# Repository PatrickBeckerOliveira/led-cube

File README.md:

# LED Cube 4×4×4 — ESP32-C3 + BLE

A 64-LED cube controlled by an ESP32-C3 SuperMini, two daisy-chained TPIC6B595 shift registers, and four layers switched by NPN-driven P-channel MOSFETs. Arduino firmware with BLE commands and five sequential animation effects.

## Firmware

Open `led_cube_ble/led_cube_ble.ino` in the Arduino IDE with the **esp32 board package by Espressif Systems** installed. Select the appropriate ESP32-C3 board (ESP32C3 Dev Module where applicable) and serial port. The code uses the BLE library included in the ESP32 package, along with `<atomic>`.

This version preserves the behavior of the animation code provided in the conversation. It has not been compiled or validated on hardware as part of this delivery; no specific ESP32 board package version has been pinned.

## Pin Mapping

| Function | GPIO |
|---|---:|
| TPIC SER IN / Data | 4 |
| TPIC SRCK / Clock | 5 |
| TPIC RCK / Latch | 6 |
| Layer 1 / NPN base | 7 |
| Layer 2 / NPN base | 8 |
| Layer 3 / NPN base | 9 |
| Layer 4 / NPN base | 10 |

Driving a layer GPIO high turns on the NPN transistor, which in turn switches on the P-channel MOSFET. A bit set to 1 in the TPIC activates the corresponding current-sinking output. The physical column order depends on the wiring.

## Using nRF Connect

1. Power on the board and connect to `Cubo_LED_4x4x4`.
2. Open service `6e400001-b5a3-f393-e0a9-e50e24dcca9e`.
3. Write UTF-8 text to characteristic `6e400002-b5a3-f393-e0a9-e50e24dcca9e`.

| Command | Action |
|---|---|
| `ON` or `1` | Start/restart the sequence |
| `OFF` or `0` | Turn off the cube |

The cube starts with all LEDs off when powered on. Disconnecting the app does not stop an ongoing animation; the device resumes advertising to allow reconnection. Commands do not require BLE authentication.

## Effects

1. Layers moving up and down.
2. Vertical columns lighting up in sequence.
3. Eight twinkling points.
4. Filling and emptying the cube layer by layer.
5. Three flashes followed by a pause.

The sequence repeats until `OFF` is received. Animation updates use `millis()`, and multiplexing uses `micros()`, with a nominal period of 2 ms per layer and a blanking interval of 30 µs. At most one layer is activated at a time. Timing and duration can be adjusted through the constants and the `updateAnimation()` function.

## Hardware Notes

- Cube supply: 5 V, with a common ground shared with the ESP. The power supply's current rating does not determine the current capacity of the SuperMini's PCB traces.
- GPIO8 and GPIO9 are boot strapping pins. The NPN base connections may interfere with startup, especially on GPIO9; using 10 kΩ resistors connected to the base showed no problems, lowering this value may cause issues.
- According to its datasheet, a TPIC6B595 powered at 5 V requires a minimum logic-high input of 0.85 × VCC = 4.25 V. Direct drive from 3.3 V GPIOs works but is not guaranteed; logic-level conversion should be implemented in the future.
- With 100 Ω column resistors and an LED forward voltage of approximately 3 V, the simplified estimate is 20 mA per LED and 320 mA for a full layer, plus the control electronics. Measure the actual current before sizing the power supply.

References: [TPIC6B595 — TI](https://www.ti.com/lit/ds/symlink/tpic6b595.pdf), [ESP32-C3 Boot Mode Selection — Espressif](https://docs.espressif.com/projects/esptool/en/latest/esp32c3/advanced-topics/boot-mode-selection.html).

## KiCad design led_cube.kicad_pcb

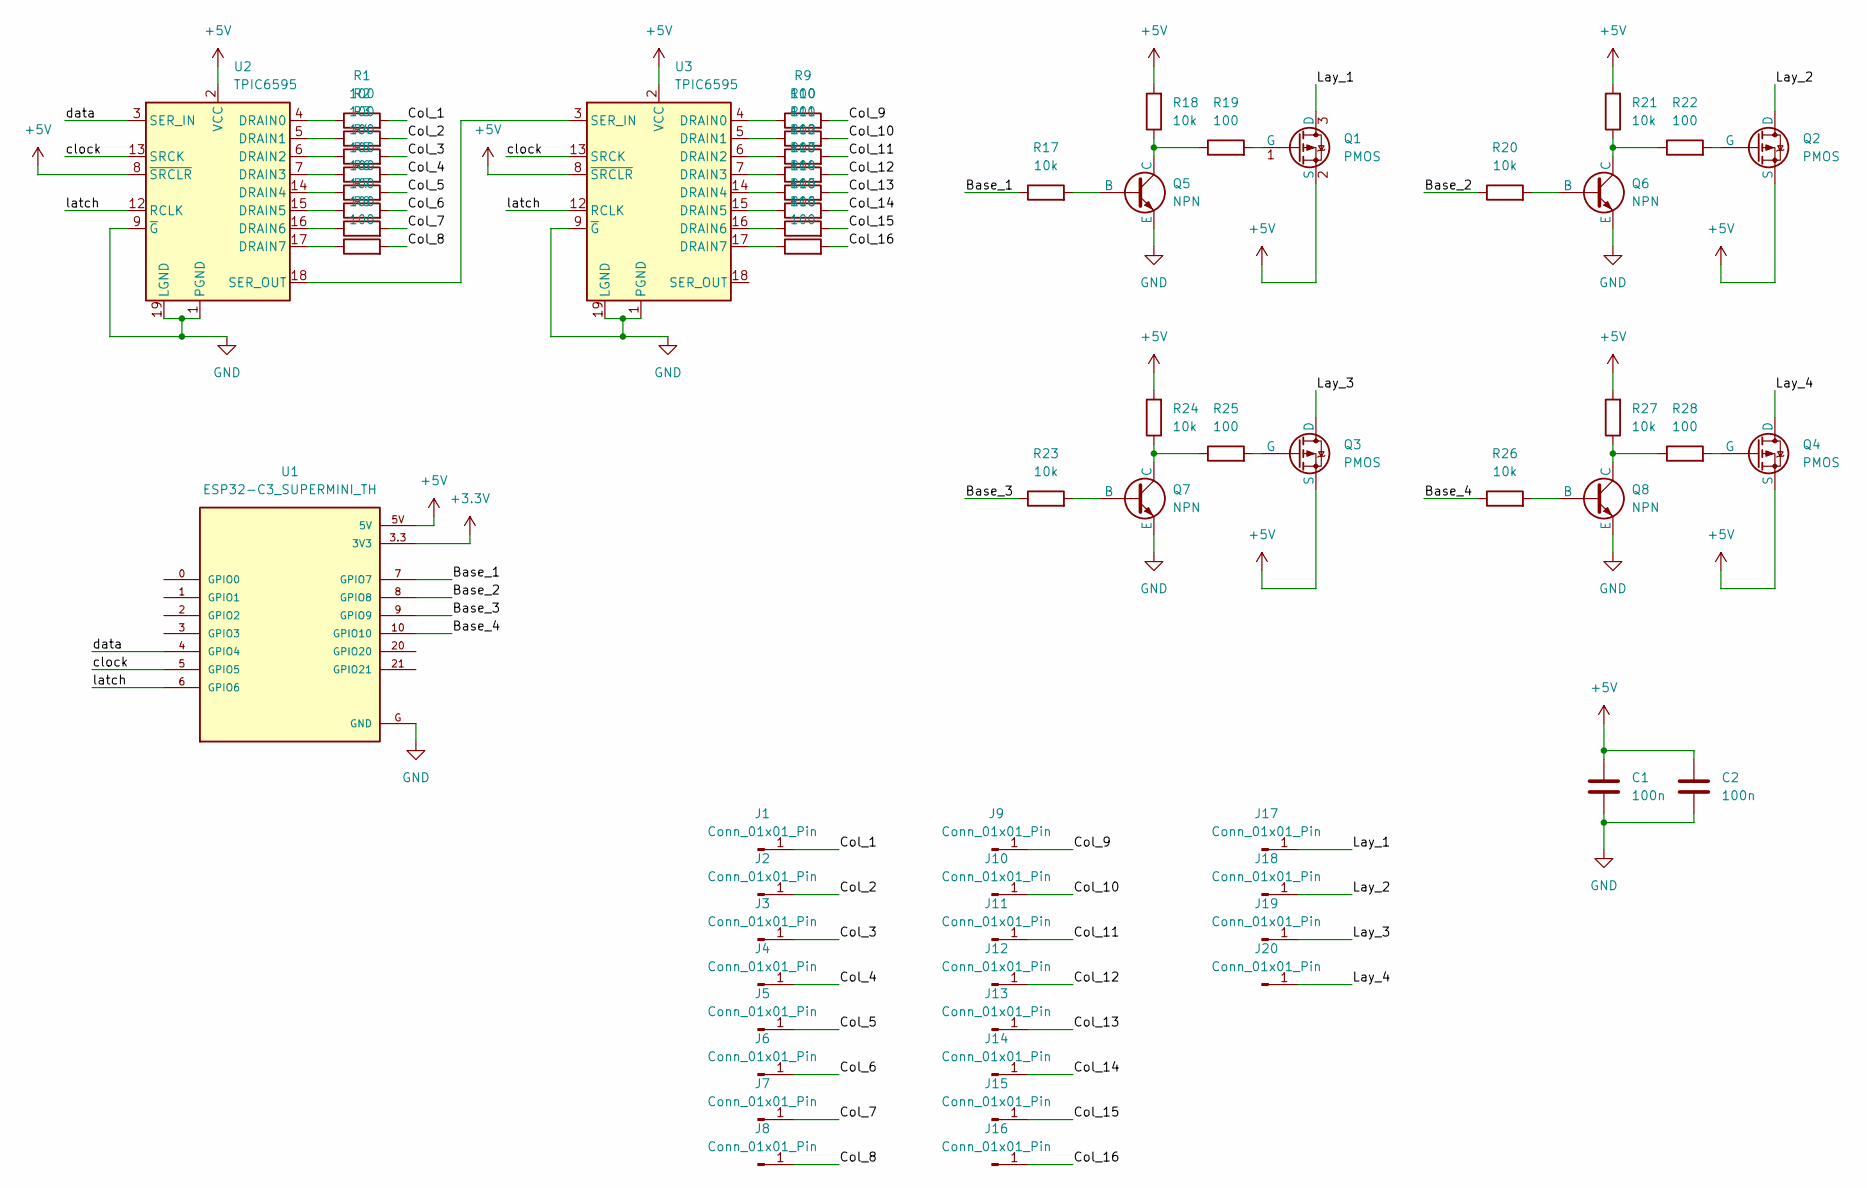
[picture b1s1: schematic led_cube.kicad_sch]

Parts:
C1, C2: 100n; C_Disc_D10.0mm_W2.5mm_P5.00mm
J1, J2, J3, J4, J5, J6, J7, J8, J9, J10, J11, J12, J13, J14, J15, J16, J17, J18, J19, J20: Conn_01x01_Pin; TestPoint_THTPad_3.0x3.0mm_Drill1.5mm
Q1, Q2, Q3, Q4: PMOS; SOT-23_Handsoldering
Q5, Q6, Q7, Q8: NPN; TO-92_HandSolder
R1, R2, R3, R4, R5, R6, R7, R8, R9, R10, R11, R12, R13, R14, R15, R16, R19, R22, R25, R28: 100; R_1206_3216Metric_Pad1.30x1.75mm_HandSolder
R17, R18, R20, R21, R23, R24, R26, R27: 10k; R_1206_3216Metric_Pad1.30x1.75mm_HandSolder
U1: ESP32-C3_SUPERMINI_TH; MODULE_ESP32-C3_SUPERMINI_TH
U2, U3: TPIC6595; CERDIP-20_W7.62mm_SideBrazed

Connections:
+3.3V: U1.3.3 (3V3)
+5V: C1.1, C2.1, Q1.2 (S), Q2.2 (S), Q3.2 (S), Q4.2 (S), R18.2, R21.2, R24.2, R27.2, U1.5V, U2.2 (VCC), U2.8 (~SRCLR), U3.2 (VCC), U3.8 (~SRCLR)
/Base_1: R17.1, U1.7 (GPIO7)
/Base_2: R20.1, U1.8 (GPIO8)
/Base_3: R23.1, U1.9 (GPIO9)
/Base_4: R26.1, U1.10 (GPIO10)
/Col_1: J1.1 (Pin_1_1), R1.2
/Col_2: J2.1 (Pin_1_1), R2.2
/Col_3: J3.1 (Pin_1_1), R3.2
/Col_4: J4.1 (Pin_1_1), R4.2
/Col_5: J5.1 (Pin_1_1), R5.2
/Col_6: J6.1 (Pin_1_1), R6.2
/Col_7: J7.1 (Pin_1_1), R7.2
/Col_8: J8.1 (Pin_1_1), R8.2
/Col_9: J9.1 (Pin_1_1), R9.2
/Col_10: J10.1 (Pin_1_1), R10.2
/Col_11: J11.1 (Pin_1_1), R11.2
/Col_12: J12.1 (Pin_1_1), R12.2
/Col_13: J13.1 (Pin_1_1), R13.2
/Col_14: J14.1 (Pin_1_1), R14.2
/Col_15: J15.1 (Pin_1_1), R15.2
/Col_16: J16.1 (Pin_1_1), R16.2
/Lay_1: J17.1 (Pin_1_1), Q1.3 (D)
/Lay_2: J18.1 (Pin_1_1), Q2.3 (D)
/Lay_3: J19.1 (Pin_1_1), Q3.3 (D)
/Lay_4: J20.1 (Pin_1_1), Q4.3 (D)
/clock: U1.5 (GPIO5), U2.13 (SRCK), U3.13 (SRCK)
/data: U1.4 (GPIO4), U2.3 (SER_IN)
/latch: U1.6 (GPIO6), U2.12 (RCLK), U3.12 (RCLK)
GND: C1.2, C2.2, Q5.3 (E), Q6.3 (E), Q7.3 (E), Q8.3 (E), U1.G (GND), U2.1 (PGND), U2.9 (~G), U2.10 (PGND), U2.11 (PGND), U2.19 (LGND), U2.20 (PGND), U3.1 (PGND), U3.9 (~G), U3.10 (PGND), U3.11 (PGND), U3.19 (LGND), U3.20 (PGND)
unnamed: Q1.1 (G), R19.2
unnamed: Q2.1 (G), R22.2
unnamed: Q3.1 (G), R25.2
unnamed: Q4.1 (G), R28.2
unnamed: Q5.2 (B), R17.2
unnamed: Q5.1 (C), R18.1, R19.1
unnamed: Q6.2 (B), R20.2
unnamed: Q6.1 (C), R21.1, R22.1
unnamed: Q7.2 (B), R23.2
unnamed: Q7.1 (C), R24.1, R25.1
unnamed: Q8.2 (B), R26.2
unnamed: Q8.1 (C), R27.1, R28.1
unnamed: R1.1, U2.4 (DRAIN0)
unnamed: R2.1, U2.5 (DRAIN1)
unnamed: R3.1, U2.6 (DRAIN2)
unnamed: R4.1, U2.7 (DRAIN3)
unnamed: R5.1, U2.14 (DRAIN4)
unnamed: R6.1, U2.15 (DRAIN5)
unnamed: R7.1, U2.16 (DRAIN6)
unnamed: R8.1, U2.17 (DRAIN7)
unnamed: U2.18 (SER_OUT), U3.3 (SER_IN)
unnamed: R9.1, U3.4 (DRAIN0)
unnamed: R10.1, U3.5 (DRAIN1)
unnamed: R11.1, U3.6 (DRAIN2)
unnamed: R12.1, U3.7 (DRAIN3)
unnamed: R13.1, U3.14 (DRAIN4)
unnamed: R14.1, U3.15 (DRAIN5)
unnamed: R15.1, U3.16 (DRAIN6)
unnamed: R16.1, U3.17 (DRAIN7)

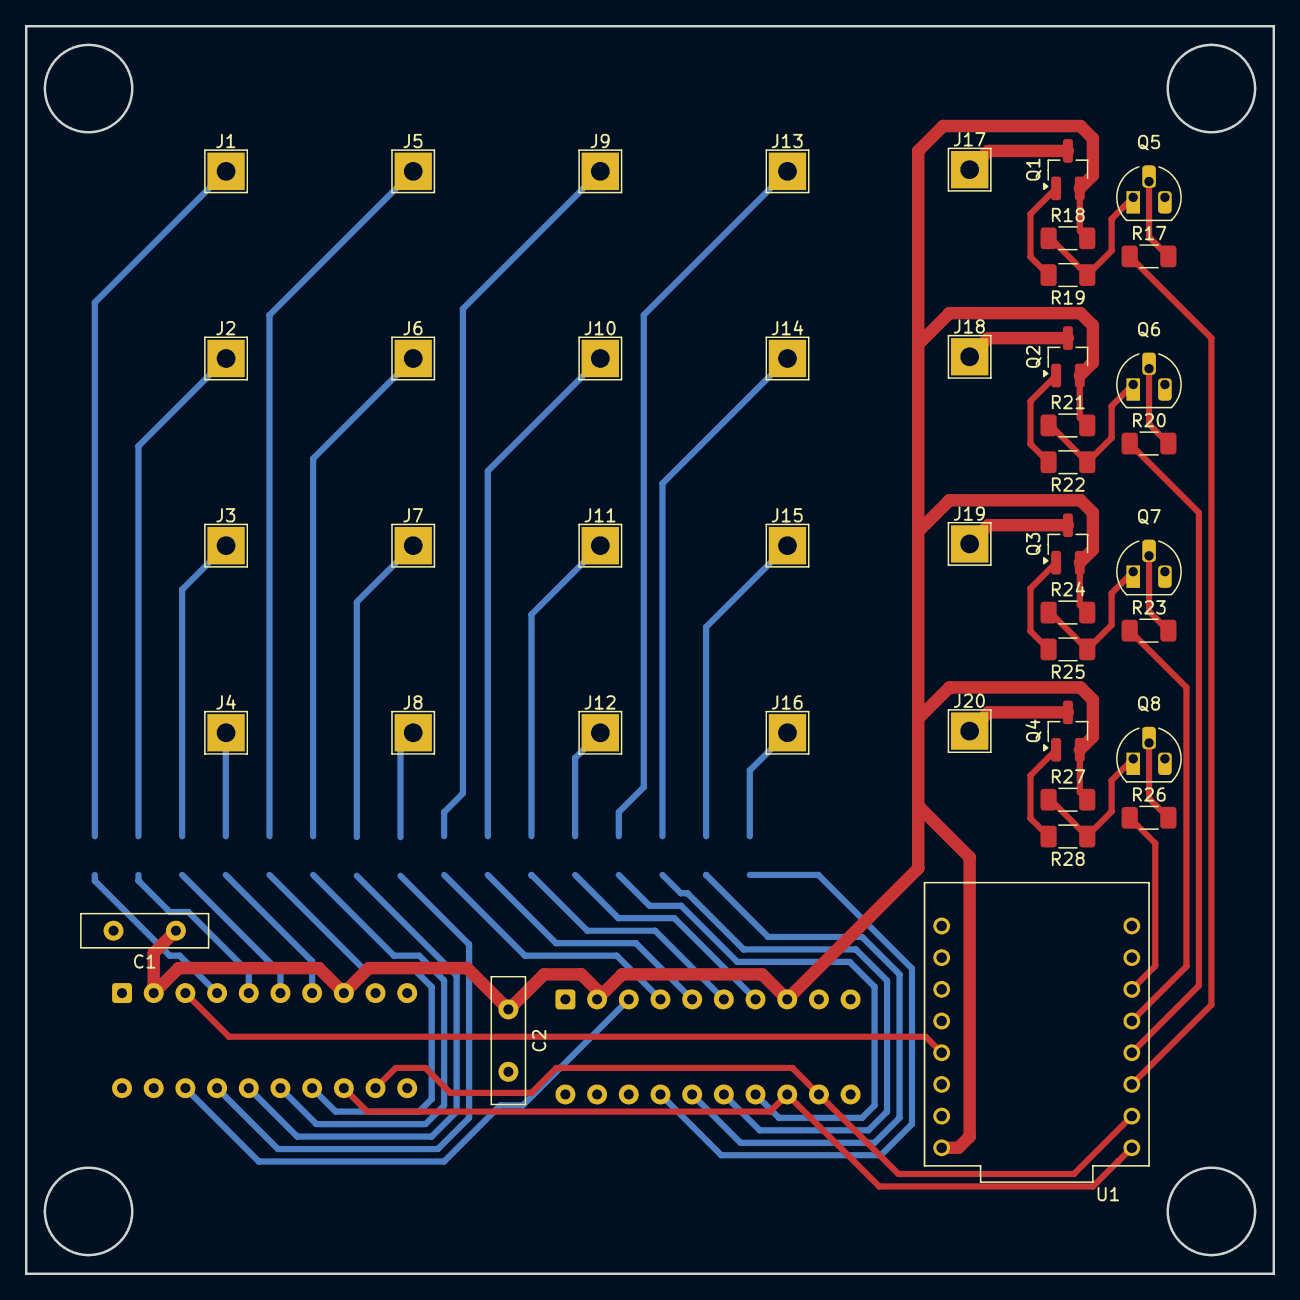
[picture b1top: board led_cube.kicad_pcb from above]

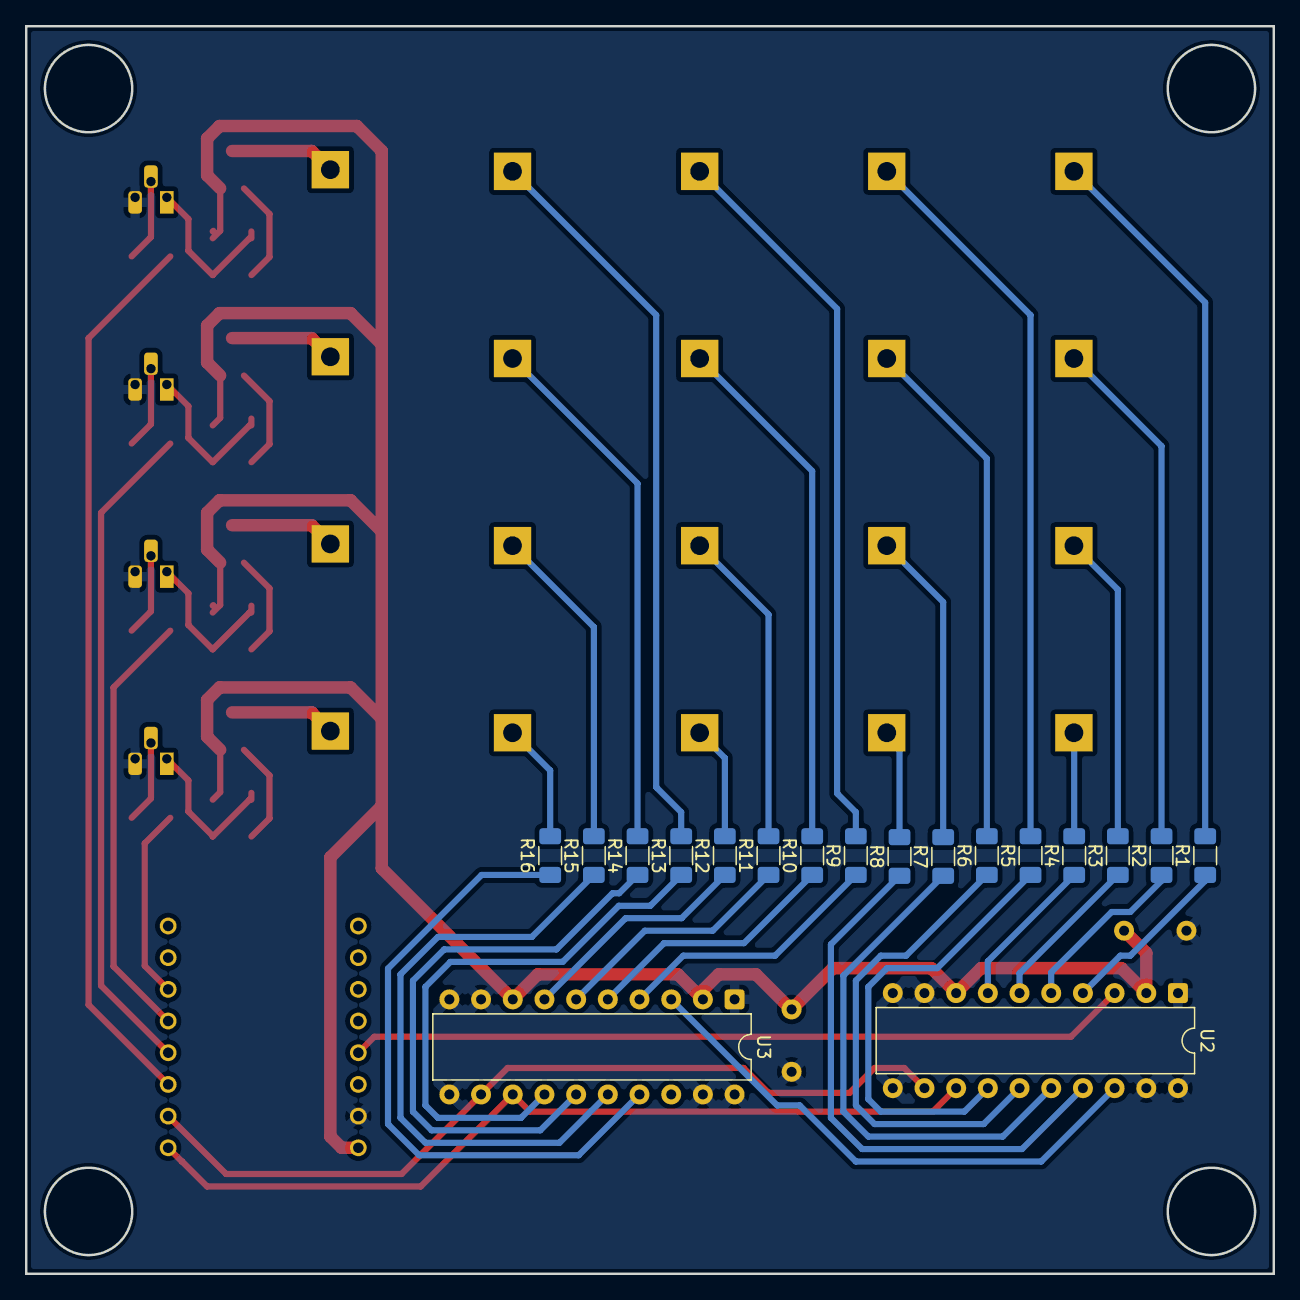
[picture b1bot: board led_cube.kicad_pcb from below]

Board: 2 copper layers, 100.0 x 100.0 mm, 61 parts (18 on the bottom side), 58 nets.
